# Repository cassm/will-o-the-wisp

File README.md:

Will-o-the-wisp
===============

60 4-channel (rgbww) SK6812 LEDs arranged over 12 pentagonal PCBs in a pentagonal dodecahedron, controlled by a teensy 3.X.
---------------------------------------------

[Photo Credit: Dee Ruane](https://www.instagram.com/everythinglightsup/)

Assembly notes:
--------------

- Each PCB has one input port and four output ports. Obviously the order and orientation in which they are wired up is critical, as co-ordinate calculation is done by static array lookup. I have not yet produced a set of instructions which represent how to assemble them in the order assumed by the software.

- I strongly advise against trying to get the firmware to compile on an arduino, as the full firmware relies on several large lookup tables being kept in memory. The code is written on the assumption that it will be run on something with at least as much capacity as a teensy 3

- You may notice that the current version of the PCBs have 6 leds one, rather than the stated 5. This is because I revised the design to give higher resolution for spacial patterns prior to learning that the fadecandy dithering routine supports a maximum of 64 leds in a string, and I have the intention of hacking in a cut-down version of fadecandy in order to support temporal dithering. However, the 64 pixel limit is a timing constraint, and is based on the assumption of 3 channels. As we are using 4 channels, this may imply a limit of (64*3 / 4 =) 48 LEDs per lantern, unless we split 3 DMA channels over 2 lanterns, which will involve much more wiring and anyway it's all very complicated and I don't want to think about it right now, but that's why.

- note that the Teensy has a logic voltage level of 3v3 and the pixels have a voltage level of 5v. I found that it mostly worked without shifting the logic level, but it was more prone to glitching. For this reason, I recommend the use of a logic level converter.

- When you're testing the module, I strongly recommend using some kind of diffuser, otherwise you'll end up with a bunch of things which look like QR codes in your vision, and that can't be good for you.

- The script which generates the palettes takes R8G8B8 encoded windows bitmaps, and requires python 3, scipy, numpy, and pillow. I intend to shortly add more interpolation options and make it way less hacky.

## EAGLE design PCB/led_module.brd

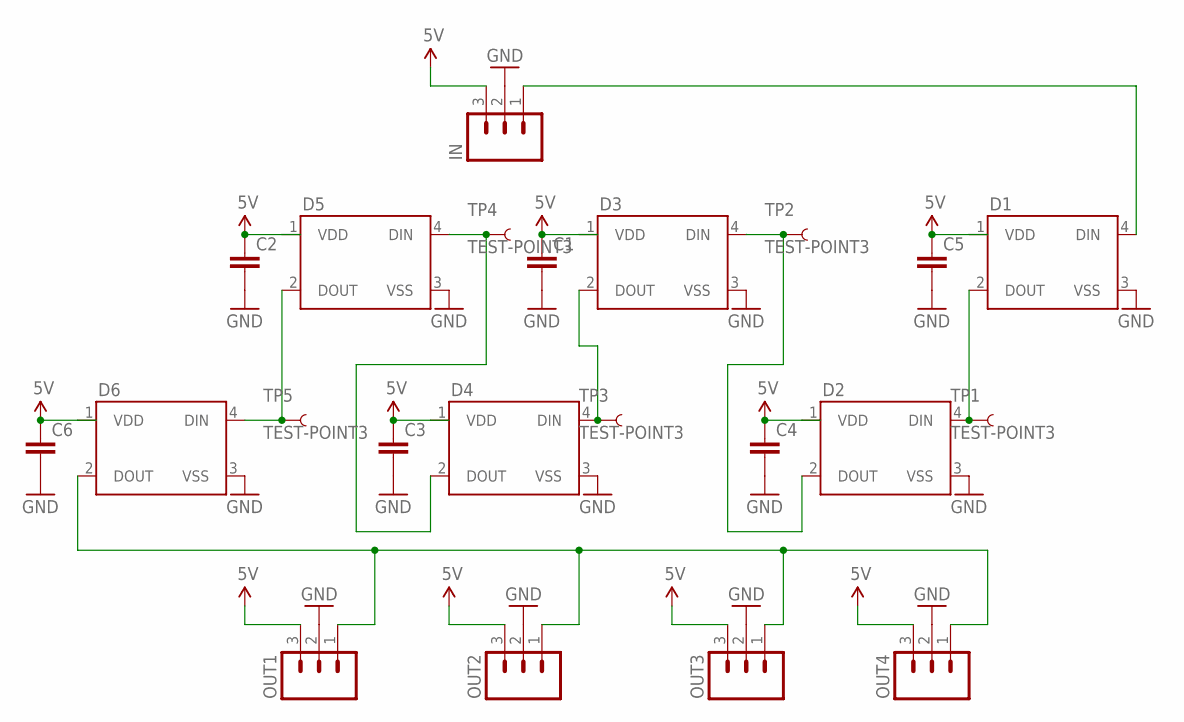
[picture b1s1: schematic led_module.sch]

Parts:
C1, C2, C3, C4, C5, C6: CAP0805; 0805
D1, D2, D3, D4, D5, D6: WS2812B
IN: M03LONGPADS; 1X03_LONGPADS
OUT1, OUT2, OUT3, OUT4: M03LONGPADS; 1X03_LONGPADS
TP1, TP2, TP3, TP4, TP5: TEST-POINT3; PAD.03X.03

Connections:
5V: C1.1, C2.1, C3.1, C4.1, C5.1, C6.1, D1.1 (VDD), D2.1 (VDD), D3.1 (VDD), D4.1 (VDD), D5.1 (VDD), D6.1 (VDD), IN.3, OUT1.3, OUT2.3, OUT3.3, OUT4.3
GND: C1.2, C2.2, C3.2, C4.2, C5.2, C6.2, D1.3 (VSS), D2.3 (VSS), D3.3 (VSS), D4.3 (VSS), D5.3 (VSS), D6.3 (VSS), IN.2, OUT1.2, OUT2.2, OUT3.2, OUT4.2
unnamed: D1.4 (DIN), IN.1
unnamed: D4.2 (DOUT), D5.4 (DIN), TP4.P$1
unnamed: D5.2 (DOUT), D6.4 (DIN), TP5.P$1
unnamed: D3.2 (DOUT), D4.4 (DIN), TP3.P$1
unnamed: D2.2 (DOUT), D3.4 (DIN), TP2.P$1
unnamed: D6.2 (DOUT), OUT1.1, OUT2.1, OUT3.1, OUT4.1
unnamed: D1.2 (DOUT), D2.4 (DIN), TP1.P$1

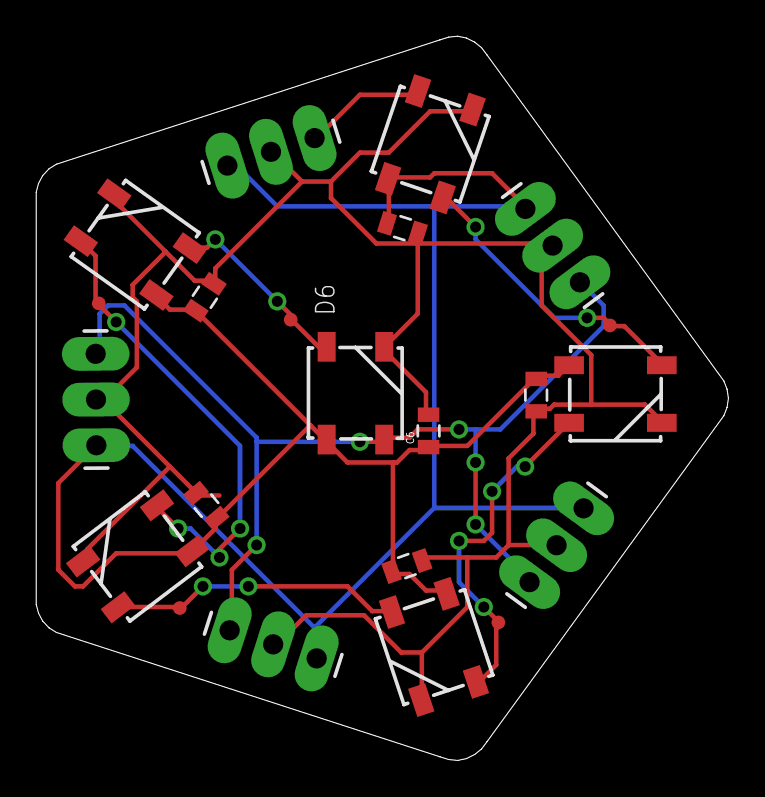
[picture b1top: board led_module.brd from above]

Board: 2 copper layers, 38.5 x 40.2 mm, 22 parts (0 on the bottom side), 9 nets.

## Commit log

2016-11-13 Discovered the correct spelling of "palette"
2016-11-13 add .gitignore
2016-11-13 continued discovery of the correct spelling of "palette"
2016-11-13 Add readme
2016-11-14 re-add palette gen script
2016-11-14 incorporate some functionality from test firmware modules
2016-11-14 corrections and clarifications to readme
2016-11-14 use math.h def of pi, and fix lib includes
2016-11-15 Add pythonry to generate HSI palettes
2016-11-19 Implement temporal dithering in octosk6812 library
    This algorithm still relies on copying the buffer for each frame, which is slower than I'd like. Plan to implement a zero copy variant later
2016-11-19 Add stress test palette
2016-11-19 Update main firmware file to bring in line with recent changes
2016-11-19 Make gamma correction and interpolation optional in palette sampler funcs
2016-11-20 Add image to readme
2016-11-20 Add credit to photo
2016-11-23 Add interrupt on pin 23 for changing patterns with a button
2016-11-23 Remove trailing whitespace (thanks, arduino ide)
2016-11-23 Add debounce interval to button isr
2016-12-24 Add fire palette, move palette arrays into progmem for compatibility with teensy 3.0
2016-12-24 Finalise colour correction factors, extend gamma correction api
2016-12-24 Add rgbw fadePixel variant
2016-12-24 Clean up palette sampling code
2016-12-24 Add EEPROM helper code
2016-12-24 Library optimisations
2016-12-24 Roll in latest hardware support from OctoWS2811
2016-12-25 Differentiate co-ordinate getter funcs
2016-12-25 Add fire palette bitmap
2016-12-25 Miraculously, still discovering correct spelling of 'palette'
2016-12-25 .gitignore additions
2016-12-25 Move to 64-stage dithering and buffer-swapping variant of LED library
2016-12-25 Big ugly commit.
    Changes include:
    - Added fire pattern algorithm
    - Added config defines
    - Added serial control
    - Added star drive pattern algorithm
    - "Bugfixes and performance enhancements"
2017-03-26 Add openpixelcontrol submodule for control using fadecandy
2017-03-26 Write basic funcs for sending 4-channel pixel values over 3-channel fadecandy firmware
2017-03-26 Move teensy firmware into subdirectory, as we are now using fadecandy
2017-03-26 use lowercase function and module names with underscores
2017-03-26 Add fadecandy layout file
    Due to each lantern having 60 4-channel LEDs, which are equivalent to 80 3-channel leds, we must use two fadecandy lines for each core
2017-03-26 Add basic control script based on raver plaid
2017-03-26 Add systemctl service files for fadecandy server and lantern control script
2017-03-26 Simplify folder naming scheme
2017-03-26 Add coordinates
    The cartesian coordinates are generated from a list of lantern locations and radii. Currently requires all lanterns to have the same rotation, as this can be marked on the core. It may be easier to f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
2017-03-26 Update location of openpixelcontrol
2017-03-26 Add script to generate cartesian coordinates based on lantern cocnfiguration
    Recalculated the spherical coordinates, which was exactly as much fun as it sounds, and put in parameters for lantern location and diameter, which should allow us to have smooth spatial patterns over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
2017-03-26 Remove old spherical coords, add third lantern to example layout
2017-03-26 Add simulate function to rgbw utils
2017-03-26 Tidying up, and add simple spatial pattern
2017-03-26 Move palettes back into root folder
2017-03-26 Add autogenerated files to .gitignore
2017-03-26 Autogenerate coordinates on script run
2017-03-26 Add palette autoprocessing and unicorn barf pattern func
2017-03-26 Default simulator=false
2017-03-27 Fix bug with channel allocation
    Apparently fcserver was automatically transposing the first two channels, which messed up the rgbw_utils transform. Fixed this in the json file, for simplicity
2017-03-27 Add colour correction for green channel in rgbw_utils. Blunt tool but will do for now
2017-03-27 Fix bug with palette autogeneration
2017-03-27 Generalise palette viewer pattern
2017-03-27 Fix error with layout file
2017-03-27 autogenerate length of pixel buffer from lantern config
2017-03-27 Use random palette selection
2017-03-27 Get pattern funcs to set pixels directly, add start and end stops for aforementioned
2017-03-27 Add provisional layout for electroworks live room
2017-03-28 Remove redundant buffer, size buffer and set pixels based on value of simulate variable
2017-03-28 Add default start and end args
2017-03-28 Add star drive pattern
2017-03-31 Add per-pixel distance from origin to coords
2017-03-31 Add simulate parameter to set_pixel, and get_pixel func
2017-03-31 Use new rgbw_utils funcs, autogenerate num_pixels, add several new patterns
    I know this commit msg leaves much to be desired but in my defence I am super tired
2017-04-01 Add shimmer pattern
2017-04-01 Make colourwaves default
2017-04-01 Update fclayout file for 24 line device
2017-04-01 Correct fclayout
2017-04-01 Default simulate to false, again
2017-04-01 Add pattern increment button
2017-04-02 Add speed control with slaved i2c device
2017-04-02 Add sketch for slaved arduino
2017-04-02 Add interrupts for controls, add sensible failure behaviour for i2c errors
2017-04-02 Fix palette handling, add random pattern handling
2017-04-02 Remove broken skyline palette
2017-04-02 Add flare handling
2017-04-02 Add second pot to analog slave, add command reads
2017-04-02 Add brightness handling, increase read frequency
2017-04-03 Improve flare and glitch handling, swap out i2c analog slave for teensy w/ usb serial
2017-04-05 Correct coordinate orientation
2017-04-05 Add inverse square func for washes and waves
2017-04-05 Make script simulation-compatible again
2017-04-05 Add auto mode, flare on switch
2017-04-06 Improve rain pattern
2017-04-06 Replace palette viewer with sky simulator, much fine tuning
2017-04-06 Improve shimmer pattern, rename
2017-04-06 Fix auto mode and flare-on-switch
2017-04-06 Fine tune rain constants
2017-04-06 Fine tune constants for make_me_one
2017-04-06 Simplify and improve skies
2017-04-06 Fix coordinate conversion
2017-04-06 Tidying up
2017-04-06 Add fire pattern
2017-04-06 Finalise flame pattern, assign button
2017-04-06 Update last mode switch on manual switch
2017-04-06 Fix bug with auto timer reset
2017-04-06 Add unicorn barf (rainbow sparkles) pattern and map to button
2017-04-06 Make unicorn barf time sensitive
2017-04-06 Add glitch option, optimise unicorn barf
2017-04-06 Extend unicorn barf cycle
2017-04-15 Compatibility changes and tidying up
    Imported project into pycharm and was made aware of a certain amount of dirty laundry. Now duly laundered.
2017-04-15 Jesus pycharm what the hell
2017-05-12 Update lantern layout for geodome
2017-05-12 Change glitch function for colour invert function
2017-05-12 Exclude fire palette from palette selection
2017-05-13 Add serial slave device for reading potentiometers
2017-05-13 Add 4 physical sliders to console
    Also replace unicorn barf pattern, which was a bit of a bodge, with the physical rgbw controls
2017-05-13 Add lantern orientation comprehension
2017-05-13 Bug fixes three
2017-05-13 Reduce pot latency
2017-05-13 Fix dumbass bug
2017-05-13 Add gamma correction on sliders, and invert range to account for wiring
2017-05-13 Correct bounds on pot reads
2017-05-13 Make brightness pot not apply to rgbw sliders
2017-05-13 Reset lantern orientations, remove fudge factor caused by moving the origina lantern at rumpus
2017-05-13 Quick and dirty spatial propogation for manual rgbw mode
    note: makes it possible for time to go backwards. use with care
2017-05-14 Slow and clean implementation of spatial propogation for manual rgbw control
2017-05-14 Bug fix
2017-05-14 Add palette for auto rgbw control
2017-05-14 Add auto colour (actually a really long palette) and replace flare button with switch for that
2017-05-14 Fix colour inversion transformation
2017-05-14 Make propogation start at the surface of the origin lantern
    or more or less so. Increases responsiveness
2017-05-14 Update and adapt patterns
    Top two rows now based on auto/manual colour - added simple wave pattern which is like star drive without the flare and vertical differentiation. May need to add an additional vertical ripple to star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
2017-05-14 Make star drive better and ditch flare
2017-05-14 Start on smooth
2017-05-14 Make crunchy create a palette around the selected colour
2017-05-14 No, you know what, start on crunchy
2017-05-14 Fix simulation bug
2017-05-15 Fix crap palette
2017-05-15 Add smaller auto palette
2017-05-15 Add high saturation palette
2017-05-15 Remove redundant palettes
2017-05-15 Add colour correction, retune time factor for new palette len, cut down unnecessary operations, start on smooth after all

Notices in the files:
parts and their libraries:
SparkFun-LED: Licensing: Creative Commons ShareAlike 4.0 International - https://creativecommons.org/licenses/by-sa/4.0
